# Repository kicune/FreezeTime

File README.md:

FreezeTime
==========

Arduino - based kitchen multi timer.

This is a simple project I started to provide our kitchen with the ability to track two (but, in a theory, with many more!) kitchen timers running simultaneously. You know, to satistfy your coffee brewing needs, when your SO is busy timing the dinner or what not.

My first approach was to buy another kitchen timer, but after some thought I decided that would be seriously uncool.
This is the second approach. :)

Some basic info:
- the schema utilizes LCD display from Nokia 5110. It's very cheap, it's very bright and easy to work with. But beware - it runs on 3V only, so if you try to reprogramm the microprocessor using USB, you MIGHT destroy it (I tried it, however, and mine survived quite a prolonged exposure to 5V). Reprogramming using external programmer (or simple 5V -> 3V level shifter) is preferred.
- the board for Eagle is 2-sided, which makes things slightly more complicated. There may be ways how to rearrange the board and make it single sided, but I wanted to have controls on the one side of the board and batteries & connector on the other side. The board is routed for a simple CNC router with 0.3 engraving V tip.
- the schematics is pretty straighforward, with microprocessor, binary encoder, LCD and switch. The only thing that is not absolutely basic here is the charge pump to sound the buzzer. I did not found a good buzzer with reasonable 3V input, so I use a simple 7660 charge pump to boost the voltage to 5V. Also, MOSFET is used to drive the buzzer, as it can sink a reasonable amount of current that would not be healthy for ATMEL / Arduino pins.
- if you decide to change the tone the buzzer beeps, beware - I encountered strange behaviour (microprocessor resetting itself...) with some frequencies.

- STL file for 3d printed enclosure will be added later.

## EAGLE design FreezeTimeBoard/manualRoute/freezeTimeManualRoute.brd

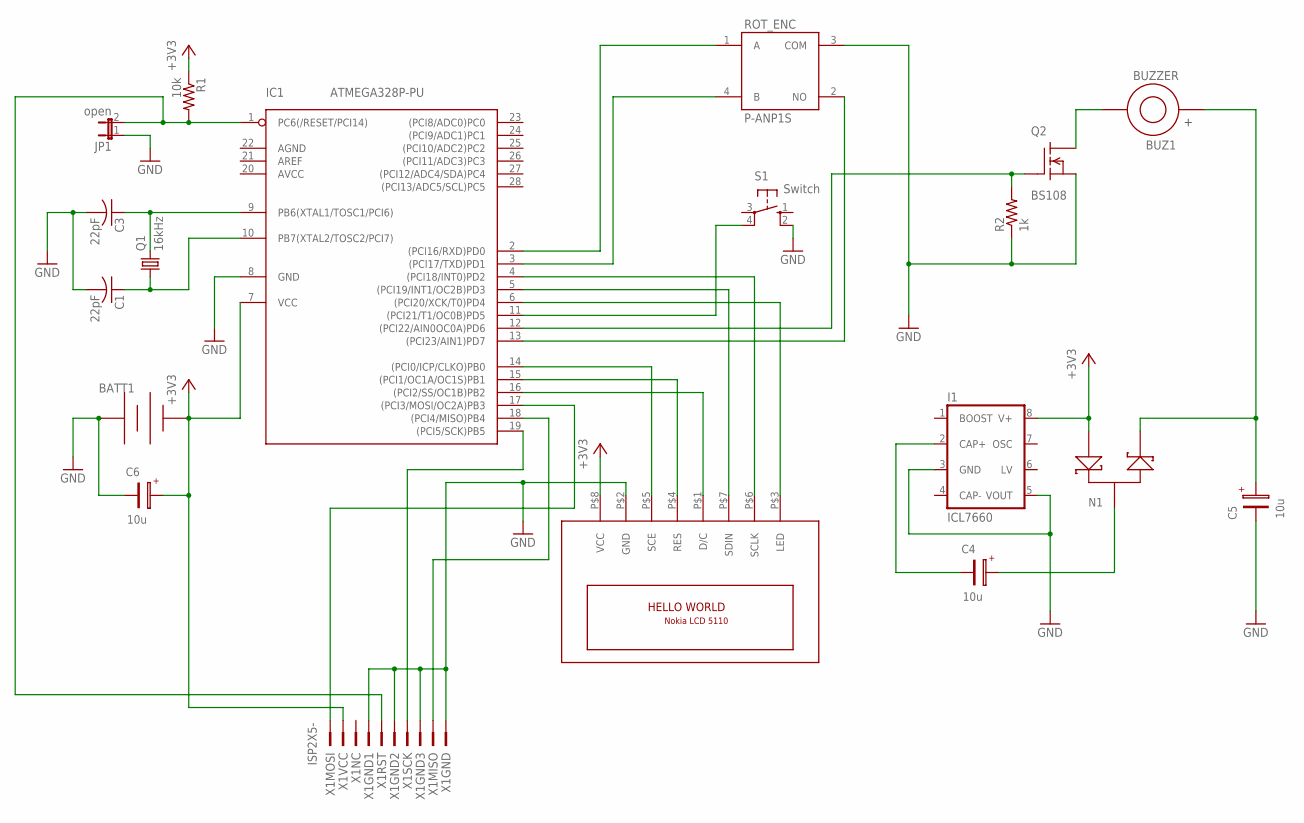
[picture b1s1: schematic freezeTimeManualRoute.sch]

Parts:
BATT1: 3VBATTERY; BH241-3A
BUZ1: BUZZER; AL1210MTE-P5R
C1, C3: 22pF; C1206
C4, C5, C6: 10u; C/6032-28R
I1: ICL7660; SO08
IC1: ATMEGA328P-PU; DIL28-3
JP1: open; JP1
LCD1: LCD_NOKIA5110; LCM5110_W
N1: BAT54S; SOT23
Q1: 16kHz; HC49U70
Q2: BS108; TO92-INLINE
R1: 10k; R1206
R2: 1k; R1206
ROT_ENC: P-ANP1S
S1: Switch; TACTS-24N
X1: ISP2X5-; PAK100/2500-10

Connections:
+3V3: BATT1.+, C6.+, I1.8 (V+), IC1.7 (VCC), LCD1.P$8 (VCC), N1.1, R1.1, X1.2
GND: BATT1.-, C1.2, C3.2, C5.-, C6.-, I1.3 (GND), I1.5 (VOUT), IC1.8 (GND), JP1.1, LCD1.P$2 (GND), Q2.3 (S), R2.1, ROT_ENC.3 (COM), S1.2 (S1), X1.4, X1.6, X1.8, X1.10
unnamed: C3.1, IC1.9 (PB6(XTAL1/TOSC1/PCI6)), Q1.2
unnamed: C1.1, IC1.10 (PB7(XTAL2/TOSC2/PCI7)), Q1.1
unnamed: IC1.13 ((PCI23/AIN1)PD7), ROT_ENC.2 (NO)
unnamed: IC1.1 (PC6(/RESET/PCI14)), JP1.2, R1.2, X1.5
unnamed: IC1.2 ((PCI16/RXD)PD0), ROT_ENC.1 (A)
unnamed: IC1.18 ((PCI4/MISO)PB4), X1.9
unnamed: IC1.3 ((PCI17/TXD)PD1), ROT_ENC.4 (B)
unnamed: IC1.15 ((PCI1/OC1A/OC1S)PB1), LCD1.P$4 (RES)
unnamed: IC1.14 ((PCI0/ICP/CLKO)PB0), LCD1.P$5 (SCE)
unnamed: IC1.16 ((PCI2/SS/OC1B)PB2), LCD1.P$1 (D/C)
unnamed: IC1.17 ((PCI3/MOSI/OC2A)PB3), X1.1
unnamed: IC1.11 ((PCI21/T1/OC0B)PD5), S1.4 (P1)
unnamed: IC1.6 ((PCI20/XCK/T0)PD4), LCD1.P$3 (LED)
unnamed: BUZ1.2, Q2.1 (D)
unnamed: IC1.19 ((PCI5/SCK)PB5), X1.7
unnamed: IC1.12 ((PCI22/AIN0OC0A)PD6), Q2.2 (G), R2.2
unnamed: IC1.5 ((PCI19/INT1/OC2B)PD3), LCD1.P$7 (SDIN)
unnamed: IC1.4 ((PCI18/INT0)PD2), LCD1.P$6 (SCLK)
unnamed: C4.-, I1.2 (CAP+)
unnamed: C4.+, N1.3
unnamed: BUZ1.1 (+), C5.+, N1.2

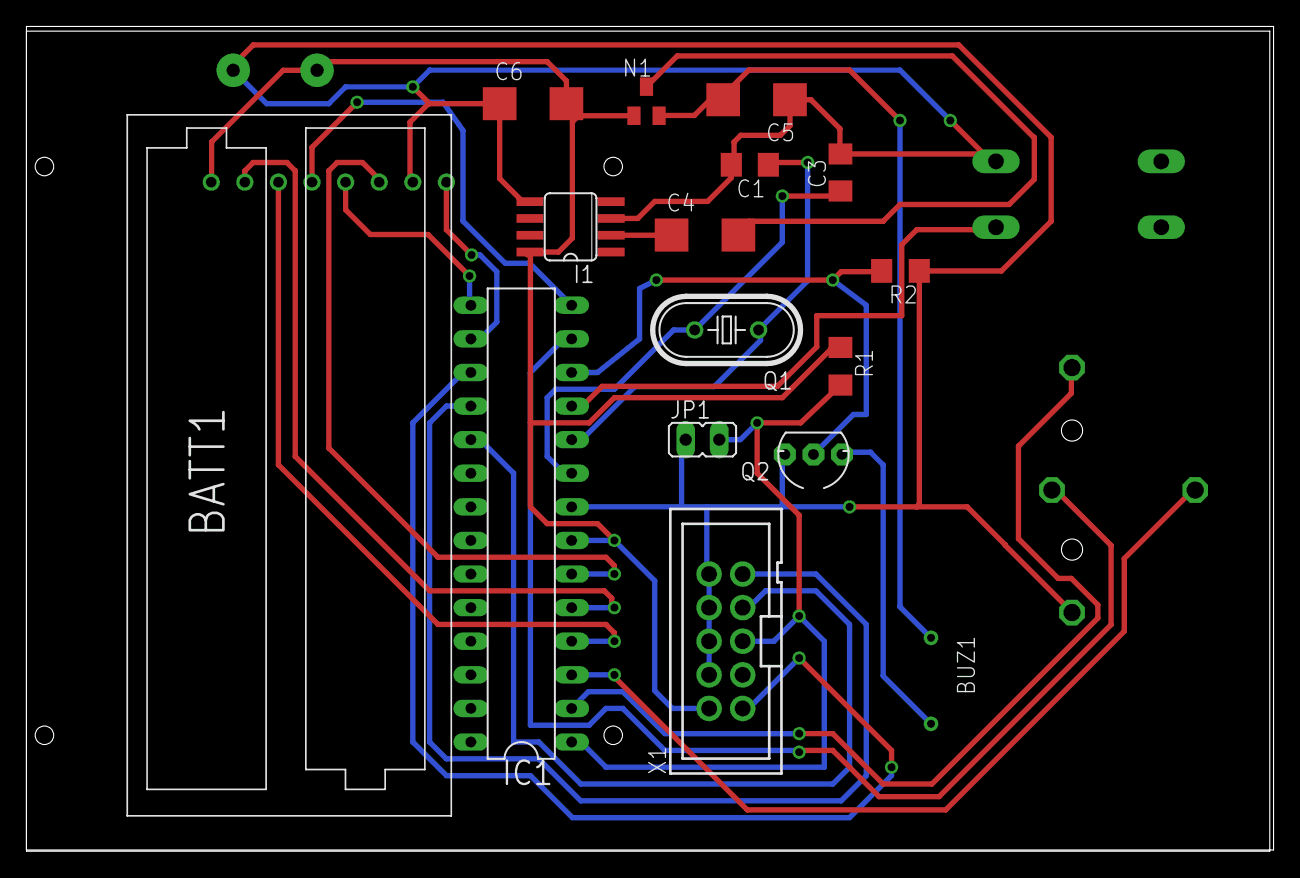
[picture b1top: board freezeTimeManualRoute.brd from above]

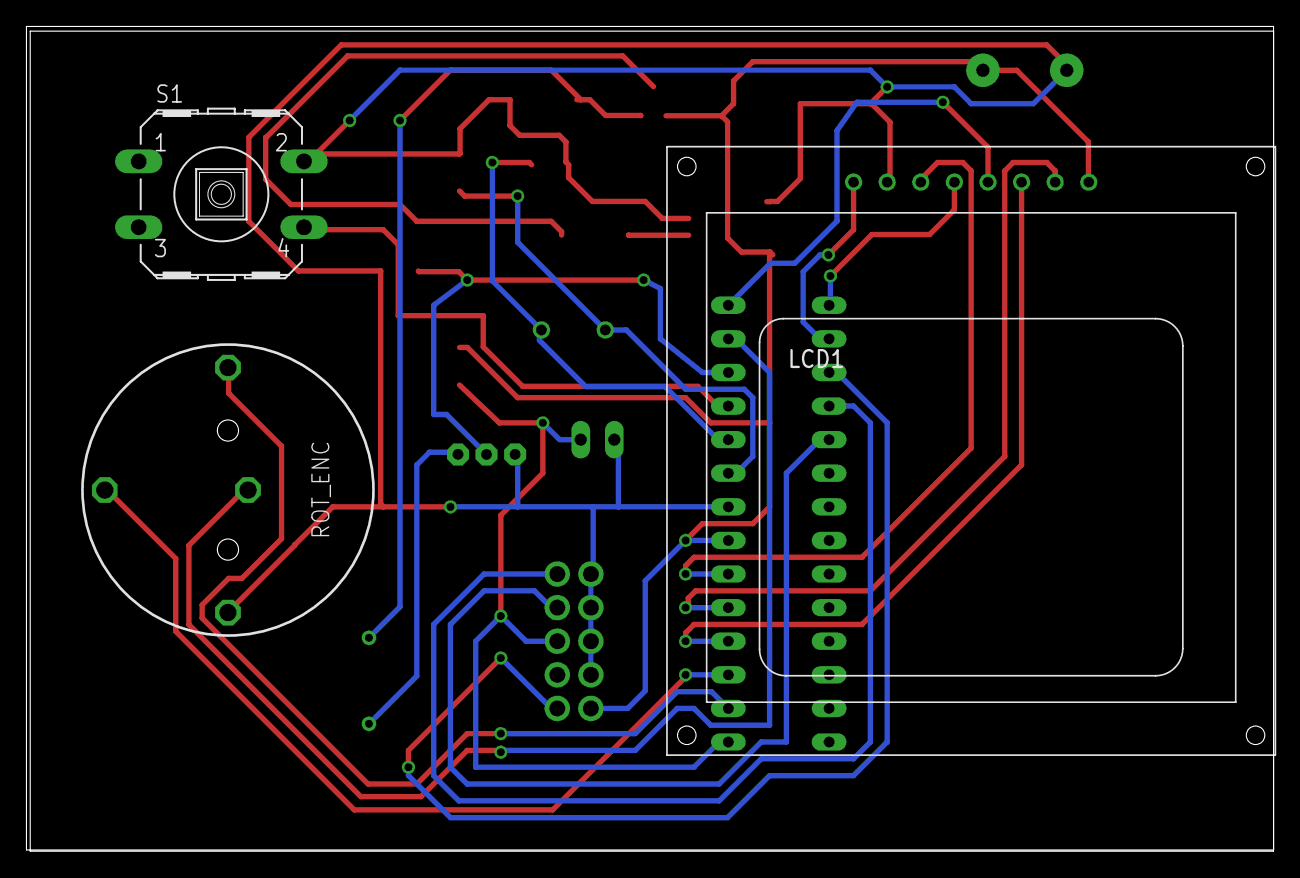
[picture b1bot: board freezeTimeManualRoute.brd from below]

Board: 2 copper layers, 94.3 x 62.4 mm, 19 parts (3 on the bottom side), 23 nets.

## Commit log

2014-12-21 Initial commit.
2014-12-21 Added the Eagle board schematics.
2014-12-31 Modified functionality for switching off the LED display while the timers run to save the batteries. LCD is lit up on interrupt.
2014-12-31 Removed backups of routed boards & fixed .gitignore to really ignore them
2016-01-03 - when the alarm is on and the focus is on an inactive alarm, switch to the active one - check the timeout during minute and second custom setting - when there is more than 15 seconds of inactivity, 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
2019-01-25 Display rotated to accomodate the new PCB
